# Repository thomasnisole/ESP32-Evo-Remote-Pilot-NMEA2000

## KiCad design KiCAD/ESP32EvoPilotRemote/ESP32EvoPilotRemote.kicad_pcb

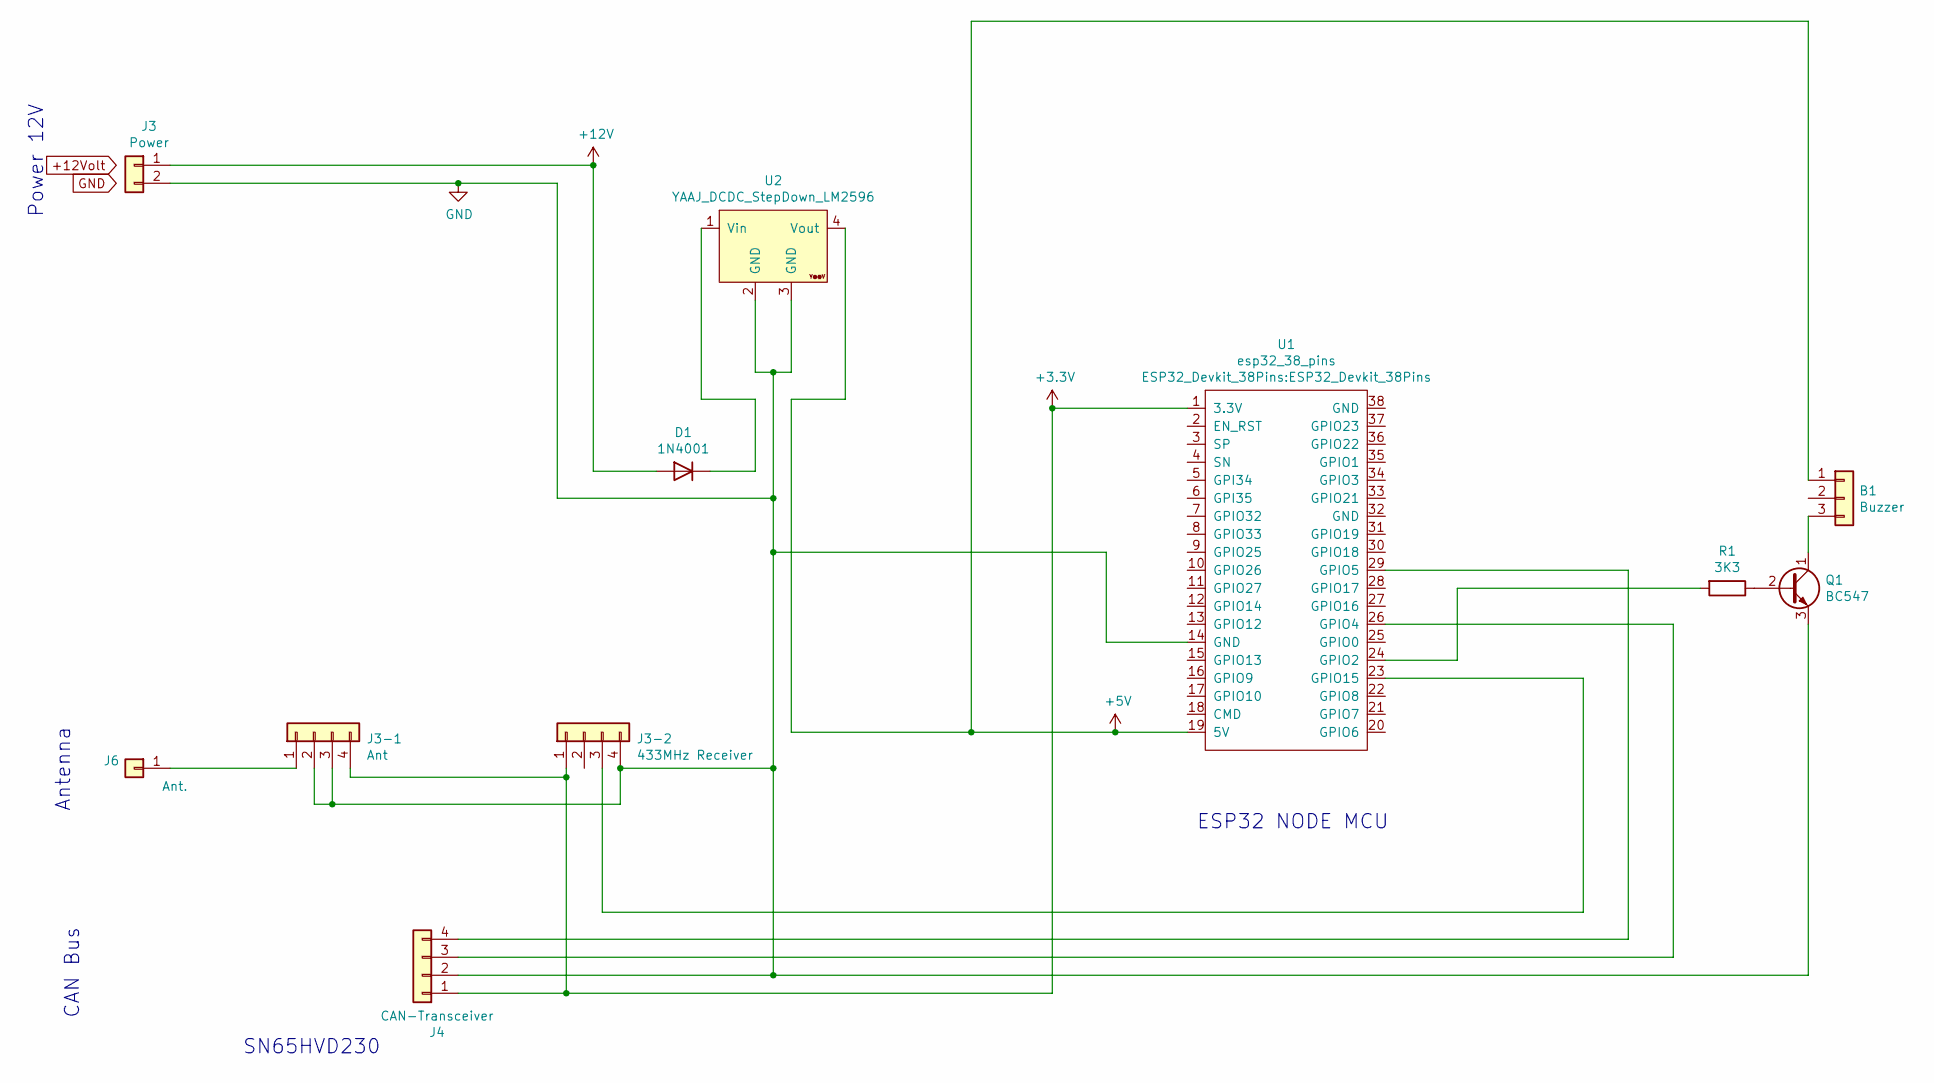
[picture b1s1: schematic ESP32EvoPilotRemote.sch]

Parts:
B1: Buzzer; PinHeader_1x03_P2.54mm_Vertical
D1: 1N4001; D_DO-41_SOD81_P10.16mm_Horizontal
J3: Power; TerminalBlock_bornier-2_P5.08mm
J3-1: Ant; PinHeader_1x04_P2.54mm_Vertical
J3-2: 433MHz Receiver; PinHeader_1x04_P2.54mm_Vertical
J4: CAN-Transceiver; PinHeader_1x04_P2.54mm_Vertical
J6: Ant.; Pin_D1.0mm_L10.0mm
Q1: BC547; TO-92_HandSolder
R1: 3K3; R_Axial_DIN0207_L6.3mm_D2.5mm_P10.16mm_Horizontal
U1: esp32_38_pins; ESP32_Devkit_38Pins
U2: YAAJ_DCDC_StepDown_LM2596

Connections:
+3V3: J3-1.4, J3-2.1, J4.1, U1.1 (3.3V)
+5V: B1.1, U1.19 (5V), U2.4 (Vout)
+12V: D1.2 (A), J3.1
GND: J3.2, J3-1.2, J3-1.3, J3-2.4, J4.2, Q1.3 (E), U1.14 (GND), U2.2 (GND), U2.3 (GND)
unnamed: B1.3, Q1.1 (C)
unnamed: D1.1 (K), U2.1 (Vin)
unnamed: J3-1.1, J6.1
unnamed: J3-2.3, U1.23 (GPIO15)
unnamed: J4.3, U1.26 (GPIO4)
unnamed: J4.4, U1.29 (GPIO5)
unnamed: Q1.2 (B), R1.1
unnamed: R1.2, U1.24 (GPIO2)

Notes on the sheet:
ESP32 NODE MCU
SN65HVD230
CAN Bus
Power 12V
Antenna

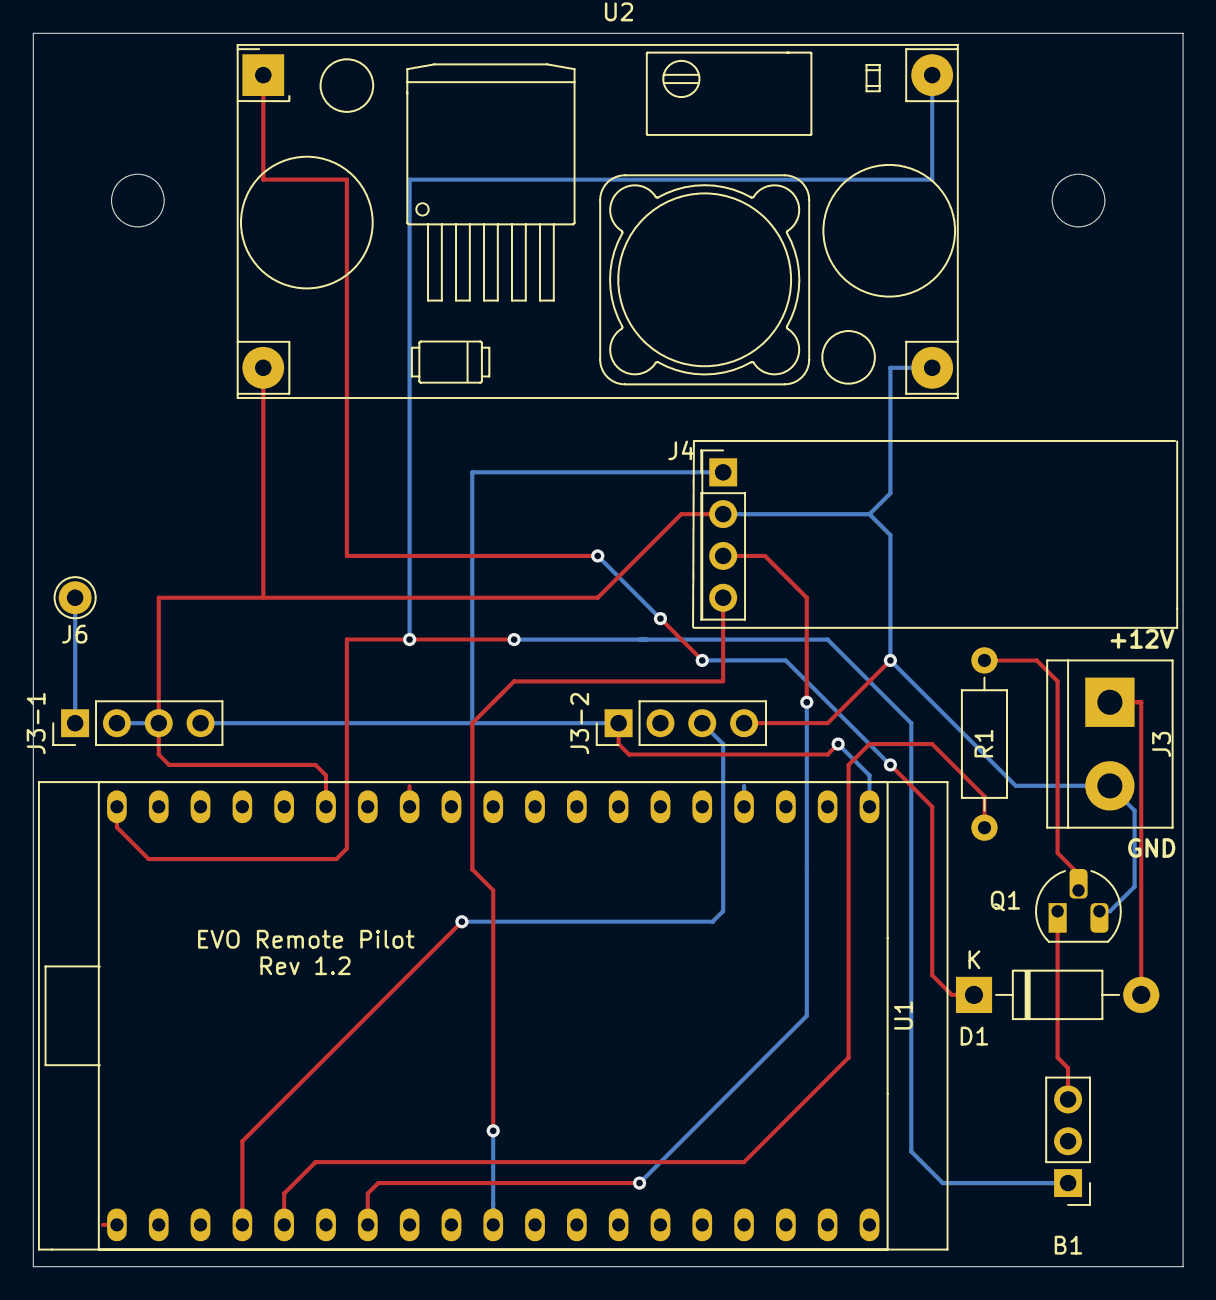
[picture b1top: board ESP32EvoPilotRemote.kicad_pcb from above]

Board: 2 copper layers, 69.8 x 74.9 mm, 13 parts (0 on the bottom side), 12 nets.

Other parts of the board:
 : MountingHole_3.2mm_M3
 #2: MountingHole_3.2mm_M3

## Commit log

2022-04-14 Add debugging
2022-04-29 feat: Configure pin
2023-03-05 feat: Update KiCAD and ino
2023-03-05 feat: Add tack and remote 2
